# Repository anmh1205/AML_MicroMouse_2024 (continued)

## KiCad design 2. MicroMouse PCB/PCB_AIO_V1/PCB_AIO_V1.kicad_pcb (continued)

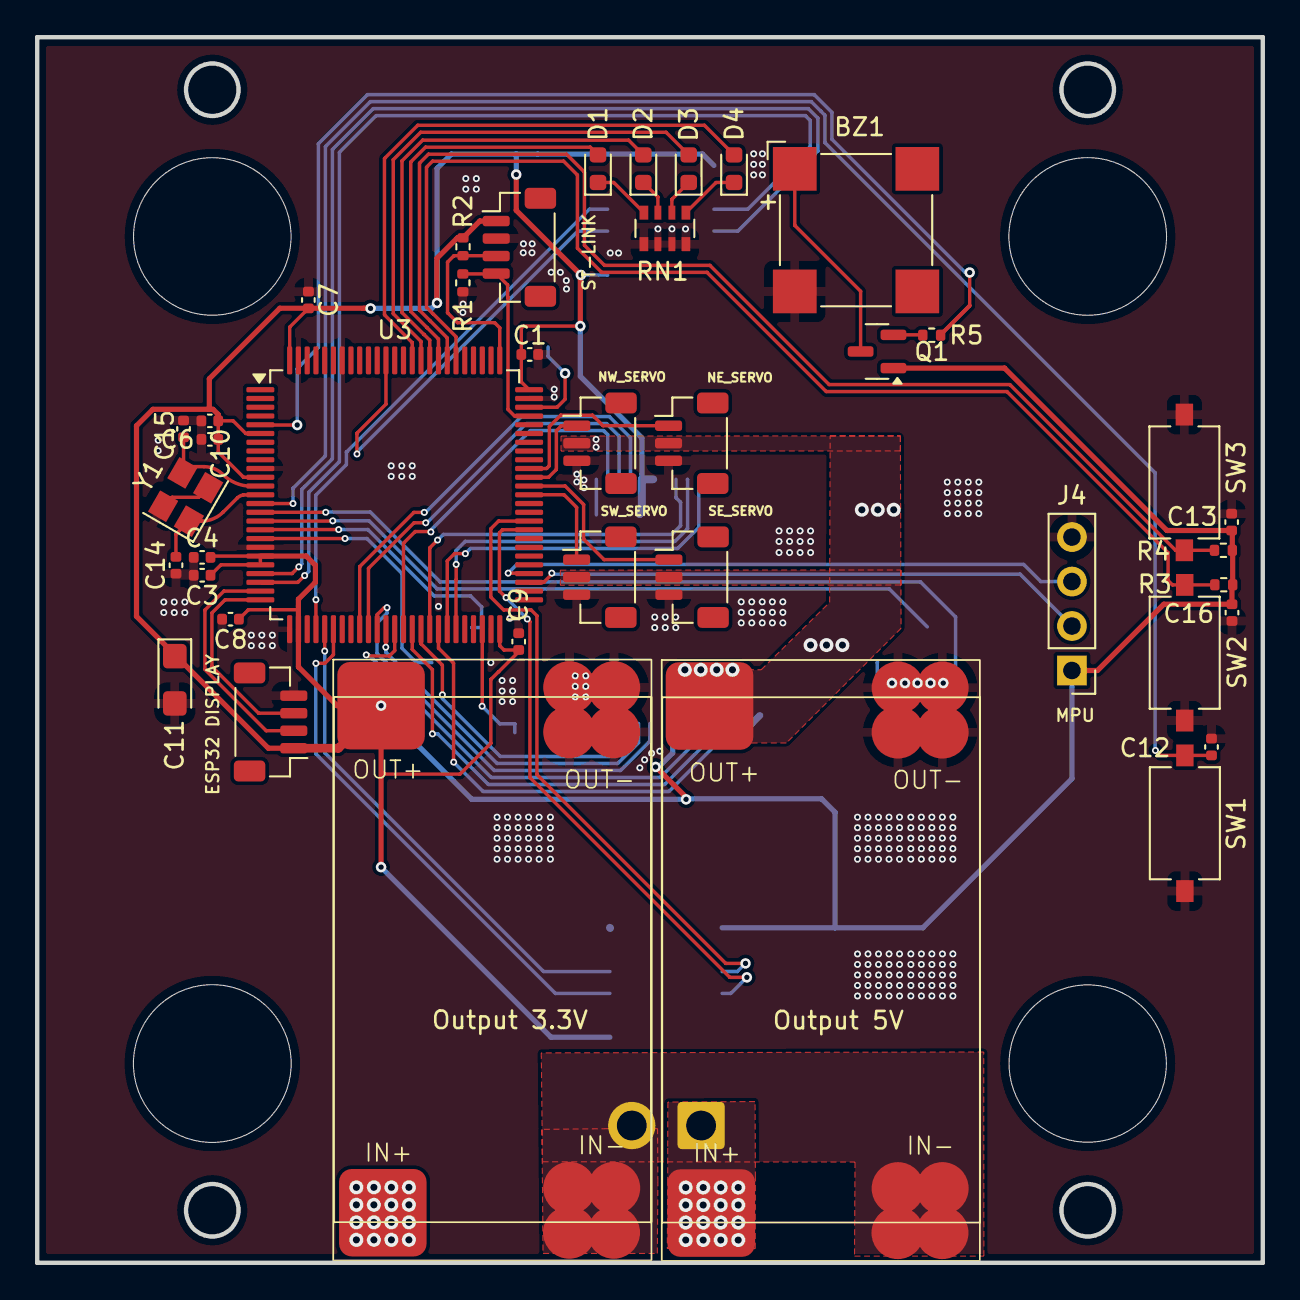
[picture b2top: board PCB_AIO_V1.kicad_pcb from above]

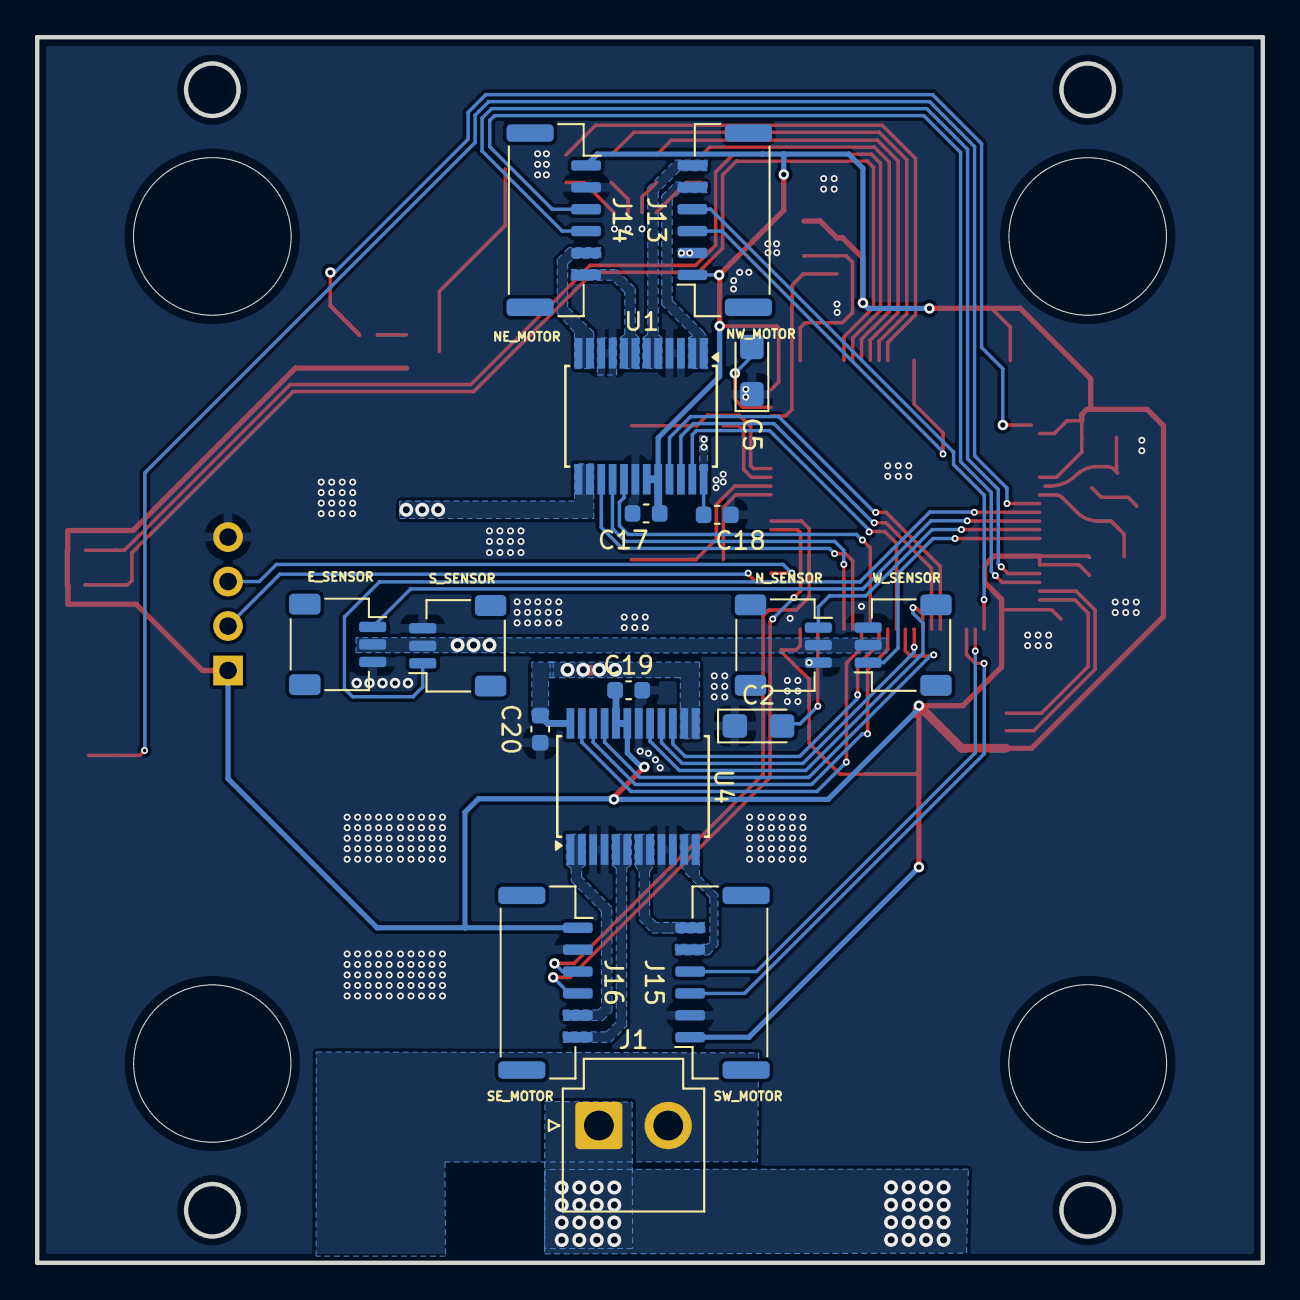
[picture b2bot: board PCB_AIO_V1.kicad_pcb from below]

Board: 2 copper layers, 70.0 x 70.0 mm, 57 parts (17 on the bottom side), 65 nets.

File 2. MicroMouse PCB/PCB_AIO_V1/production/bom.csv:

Designator,Footprint,Quantity,Value,LCSC Part #
BZ1,MagneticBuzzer_CUI_CMT-8504-100-SMT,1,Buzzer,
"C1, C10, C12, C13, C16, C3, C4, C6, C7, C8, C9",0402,11,100nF,
C11,CP_EIA-3216-10_Kemet-I,1,4.7uF,
"C14, C15",0402,2,15pF,
"C17, C18, C19, C20",0603,4,10uF,
"C2, C5",CP_EIA-3216-10_Kemet-I,2,2.2uF,
"D1, D2, D3, D4",0603,4,3VL,
J1,JST_VH_B2P-VH-B_1x02_P3.96mm_Vertical,1,Conn_01x02_Pin,
"J10, J11, J12, J9",JST_SH_SM03B-SRSS-TB_1x03-1MP_P1.00mm_Horizontal,4,Conn_01x03_Pin,
"J13, J14, J15, J16",JST_GH_SM06B-GHS-TB_1x06-1MP_P1.25mm_Horizontal,4,Conn_01x06_Pin,
J2,JST_SH_BM04B-SRSS-TB_1x04-1MP_P1.00mm_Vertical,1,STLINK,
J3,JST_SH_BM04B-SRSS-TB_1x04-1MP_P1.00mm_Vertical,1,MPU,
J4,PinHeader_1x04_P2.54mm_Vertical,1,MPU,
"J5, J6, J7, J8",JST_SH_BM03B-SRSS-TB_1x03-1MP_P1.00mm_Vertical,4,Conn_01x03_Pin,
Q1,SOT-23,1,S8550,
"R1, R2",0402,2,10K,
"R3, R4, R5",0402,3,1K,
RN1,R_Array_Convex_4x0603,1,R_Pack04,
"SW1, SW2, SW3",SW_Tactile_SPST_NO_Straight_CK_PTS636Sx25SMTRLFS,3,SW_Push,
"U1, U4",SSOP-24_5.3x8.2mm_P0.65mm,2,TB6612FNG,
U2,Mini560_5A,1,Output 5V,
U3,LQFP-100_14x14mm_P0.5mm,1,STM32H743VITx,
U5,Mini560_5A,1,Output 3.3V,
Y1,Crystal_SMD_3225-4Pin_3.2x2.5mm,1,Crystal_GND24_Small,

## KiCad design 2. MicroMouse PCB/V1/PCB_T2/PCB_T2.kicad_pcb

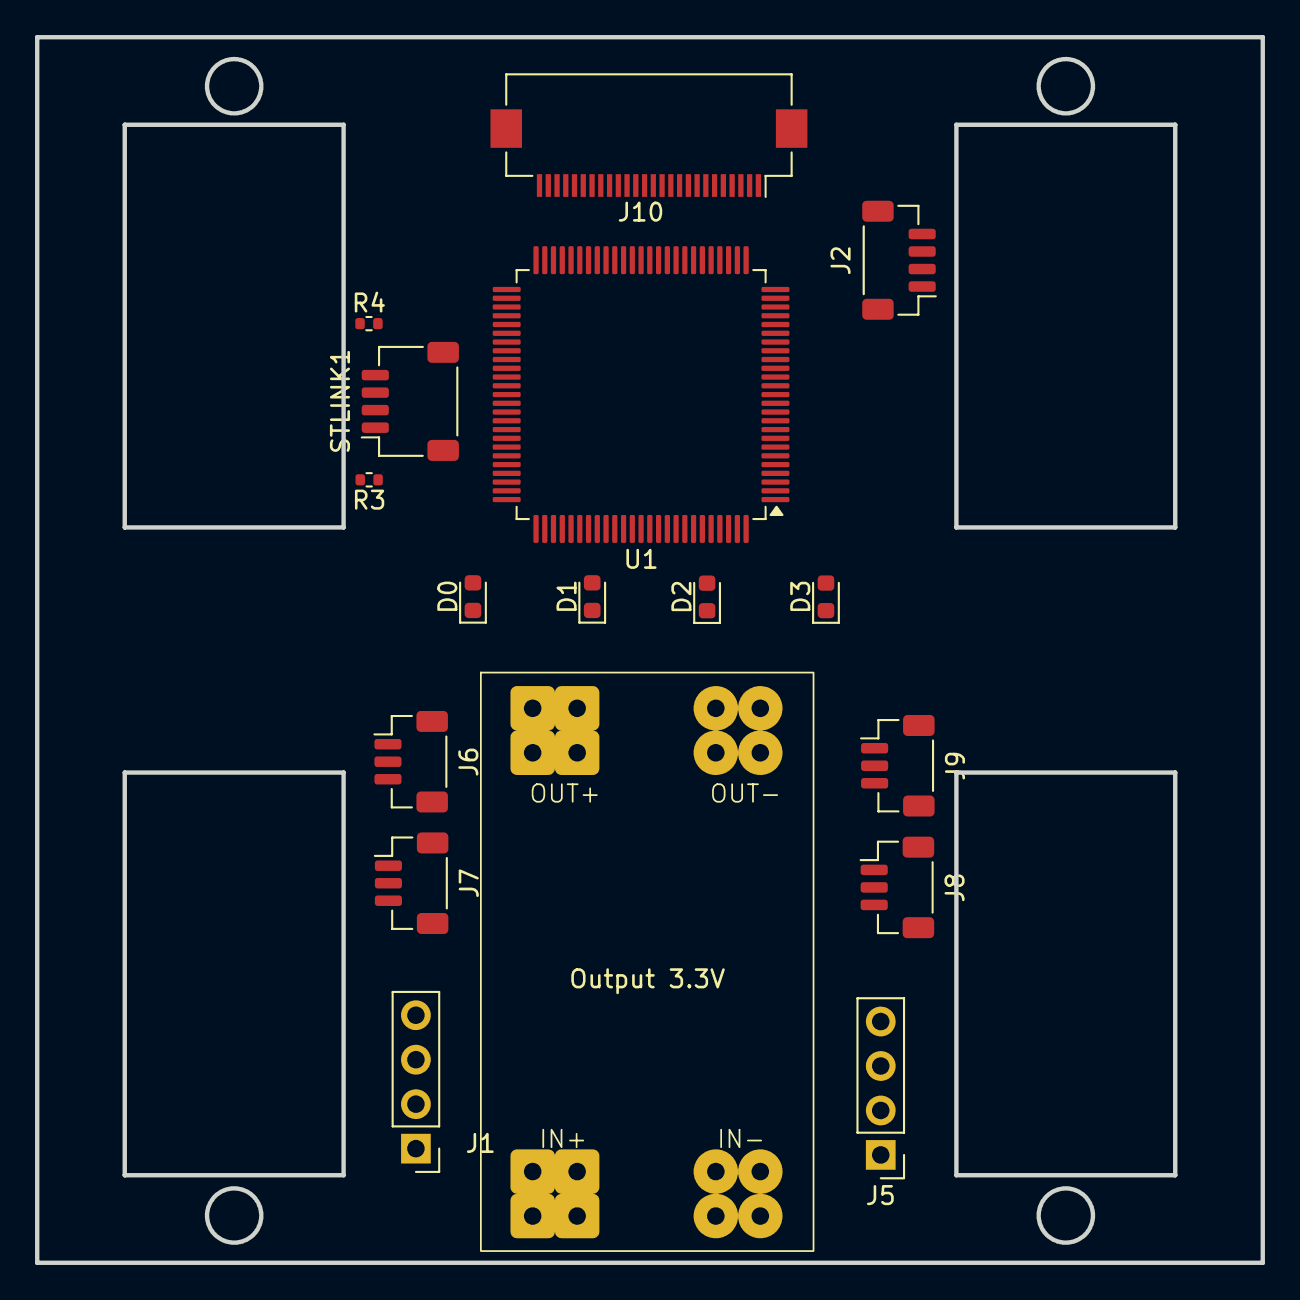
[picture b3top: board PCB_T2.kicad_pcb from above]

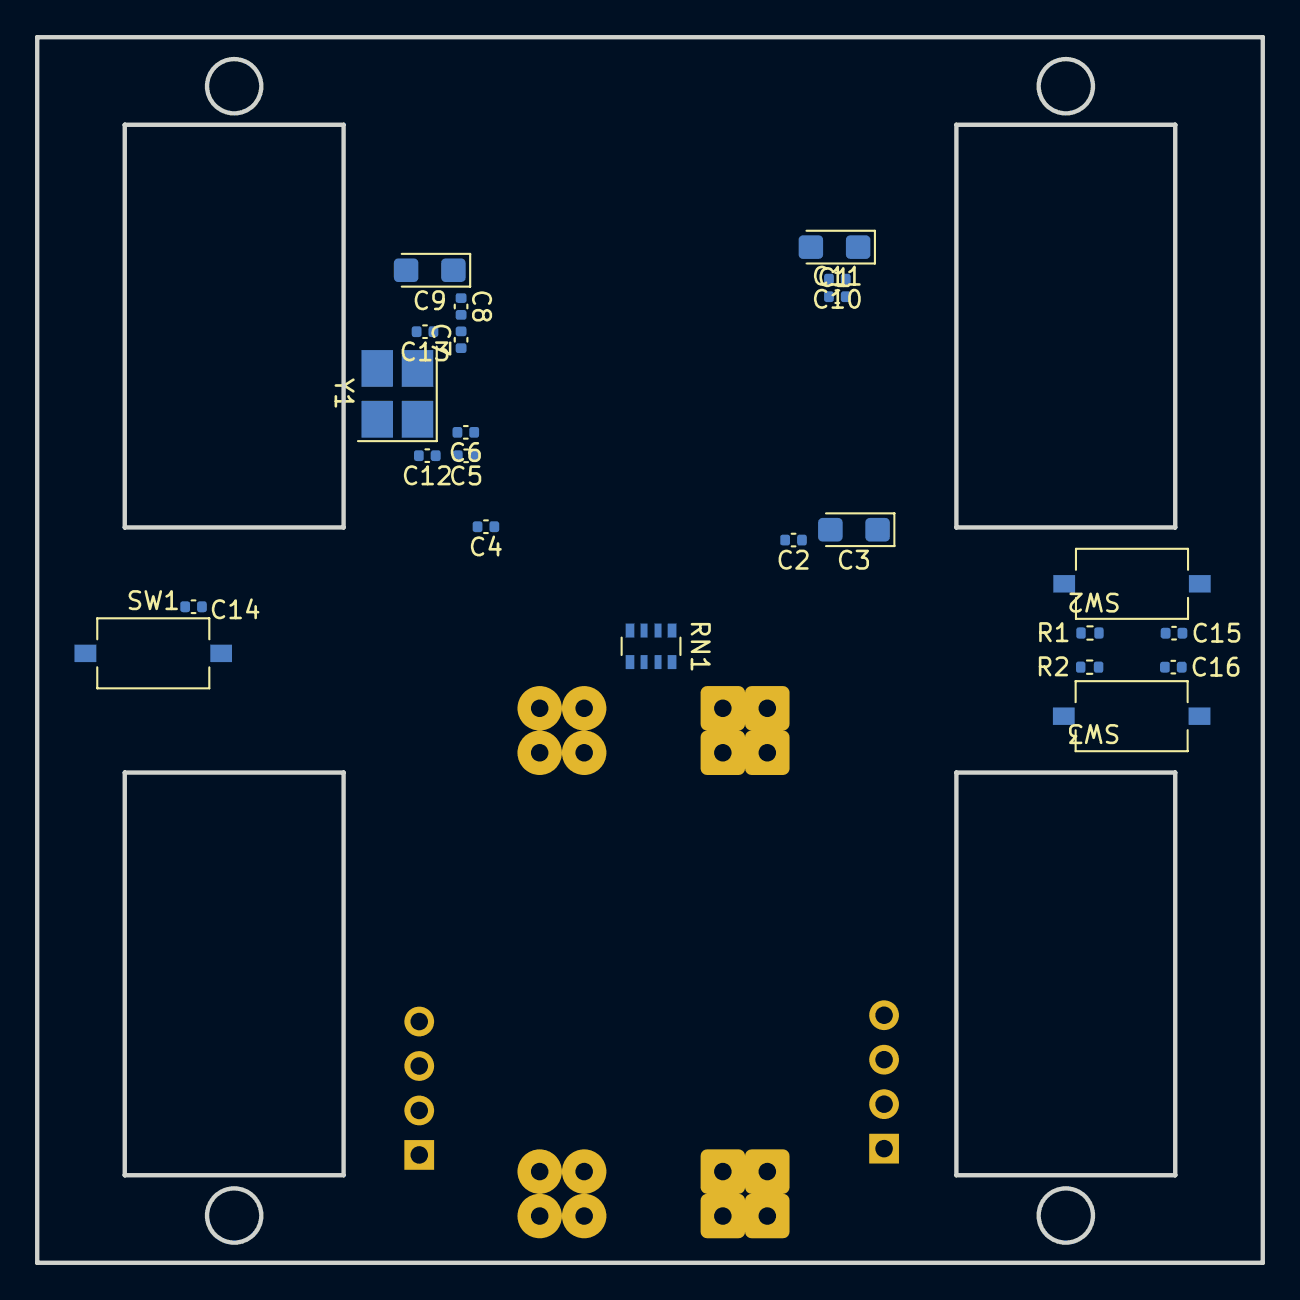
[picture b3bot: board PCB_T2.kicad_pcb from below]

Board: 2 copper layers, 70.0 x 70.0 mm, 40 parts (23 on the bottom side), 52 nets, no tracks yet.

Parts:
C1, C3: 2.2uF; CP_EIA-3216-10_Kemet-I
C2, C4, C5, C6, C7, C8, C10, C11, C14, C15, C16: 100nF; C_0402_1005Metric
C9: 4.7uF; CP_EIA-3216-10_Kemet-I
C12, C13: 15pF; C_0402_1005Metric
D0, D1, D2, D3: 3VL; LED_0603_1608Metric
J1: MPU; PinHeader_1x04_P2.54mm_Vertical
J2: MPU; JST_SH_BM04B-SRSS-TB_1x04-1MP_P1.00mm_Vertical
J5: Conn_01x04_Pin; PinHeader_1x04_P2.54mm_Vertical
J6, J7, J8, J9: Conn_01x03_Pin; JST_SH_BM03B-SRSS-TB_1x03-1MP_P1.00mm_Vertical
J10: Conn_01x26_Socket; Hirose_FH12-26S-0.5SH_1x26-1MP_P0.50mm_Horizontal
R1, R2: 1K; R_0402_1005Metric
R3, R4: 10K; R_0402_1005Metric
RN1: R_Pack04; R_Array_Convex_4x0603
STLINK1: STLINK; JST_SH_SM04B-SRSS-TB_1x04-1MP_P1.00mm_Horizontal
SW1, SW2, SW3: SW_Push; SW_Tactile_SPST_NO_Straight_CK_PTS636Sx25SMTRLFS
U1: STM32H743VIT6; LQFP-100_14x14mm_P0.5mm
U2: Output 3.3V; Mini560_5A
Y1: 48MHz; Crystal_SMD_3225-4Pin_3.2x2.5mm_HandSoldering

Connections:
+3.3V: C2.2, C4.1, C5.1, C6.1, C7.1, C8.1, C9.1, C10.2, C11.1, C15.2, C16.2, J1.1, J2.1, R1.2, R2.2, R3.2, STLINK1.1, U1.6 (VBAT), U1.11 (VDD), U1.19 (VDD), U1.21 (VREF+), U1.22 (VDDA), U1.28 (VDD), U1.50 (VDD), U1.75 (VDD), U1.100 (VDD)
+5V: J5.3, J6.2, J7.2, J8.2, J9.2
/BUTTON_0: R1.1, SW2.2, U1.81 (PD0)
/BUTTON_1: R2.1, SW3.2, U1.82 (PD1)
/E_TOF: J10.4, U1.18 (PC3)
/LED_0: D0.2 (A), U1.83 (PD2)
/LED_1: D1.2 (A), U1.84 (PD3)
/LED_2: D2.2 (A), U1.85 (PD4)
/LED_3: D3.2 (A), U1.86 (PD5)
/NE_ENC_A: J10.23, U1.23 (PA0)
/NE_ENC_B: J10.24, U1.24 (PA1)
/NE_IN1: J10.20, U1.43 (PE12)
/NE_IN2: J10.21, U1.46 (PE15)
/NE_PWM: J10.22, U1.45 (PE14)
/NE_SERVO: J9.1, U1.66 (PC9)
/NRST: C14.2, SW1.2, U1.14 (NRST)
/NW_ENC_A: J10.8, U1.30 (PA5)
/NW_ENC_B: J10.9, U1.89 (PB3)
/NW_IN1: J10.5, U1.35 (PB0)
/NW_IN2: J10.6, U1.36 (PB1)
/NW_PWM: J10.7, U1.40 (PE9)
/NW_SERVO: J6.1, U1.63 (PC6)
/N_TOF: J10.1, U1.15 (PC0)
/PH0: C12.2, U1.12 (PH0), Y1.1
/PH1: C13.2, U1.13 (PH1), Y1.2
/SE_ENC_A: J10.18, U1.59 (PD12)
/SE_ENC_B: J10.19, U1.60 (PD13)
/SE_IN1: J10.15, U1.39 (PE8)
/SE_IN2: J10.16, U1.41 (PE10)
/SE_PWM: J10.17, U1.44 (PE13)
/SE_SERVO: J8.1, U1.65 (PC8)
/SWCLK: R3.1, STLINK1.3, U1.76 (PA14)
/SWDIO: R4.2, STLINK1.4, U1.72 (PA13)
/SW_ENC_A: J10.13, U1.31 (PA6)
/SW_ENC_B: J10.14, U1.32 (PA7)
/SW_IN1: J10.10, U1.37 (PB2)
/SW_IN2: J10.11, U1.38 (PE7)
/SW_PWM: J10.12, U1.42 (PE11)
/SW_SERVO: J7.1, U1.64 (PC7)
/S_TOF: J10.3, U1.17 (PC2)
/USART1_RX: J1.3, U1.54 (PB15)
/USART1_TX: J1.2, U1.53 (PB14)
/USART2_RX: J2.3, U1.26 (PA3)
/USART2_TX: J2.2, U1.25 (PA2)
/W_TOF: J10.2, U1.16 (PC1)
GND: C1.1, C2.1, C3.1, C4.2, C5.2, C6.2, C7.2, C8.2, C9.2, C10.1, C11.2, C12.1, C13.1, C14.1, C15.1, C16.1, J1.4, J2.4, J5.4, J6.3, J7.3, J8.3, J9.3, R4.1, RN1.5 (R4.2), RN1.6 (R3.2), RN1.7 (R2.2), RN1.8 (R1.2), STLINK1.2, SW1.1, SW2.1, SW3.1, U1.10 (VSS), U1.20 (VSSA), U1.27 (VSS), U1.74 (VSS), U1.94 (BOOT0), U1.99 (VSS)
unnamed: D0.1 (K), RN1.1 (R1.1)
unnamed: D1.1 (K), RN1.2 (R2.1)
unnamed: D2.1 (K), RN1.3 (R3.1)
unnamed: D3.1 (K), RN1.4 (R4.1)
unnamed: C1.2, U1.49 (VCAP_1)
unnamed: C3.2, U1.73 (VCAP_2)

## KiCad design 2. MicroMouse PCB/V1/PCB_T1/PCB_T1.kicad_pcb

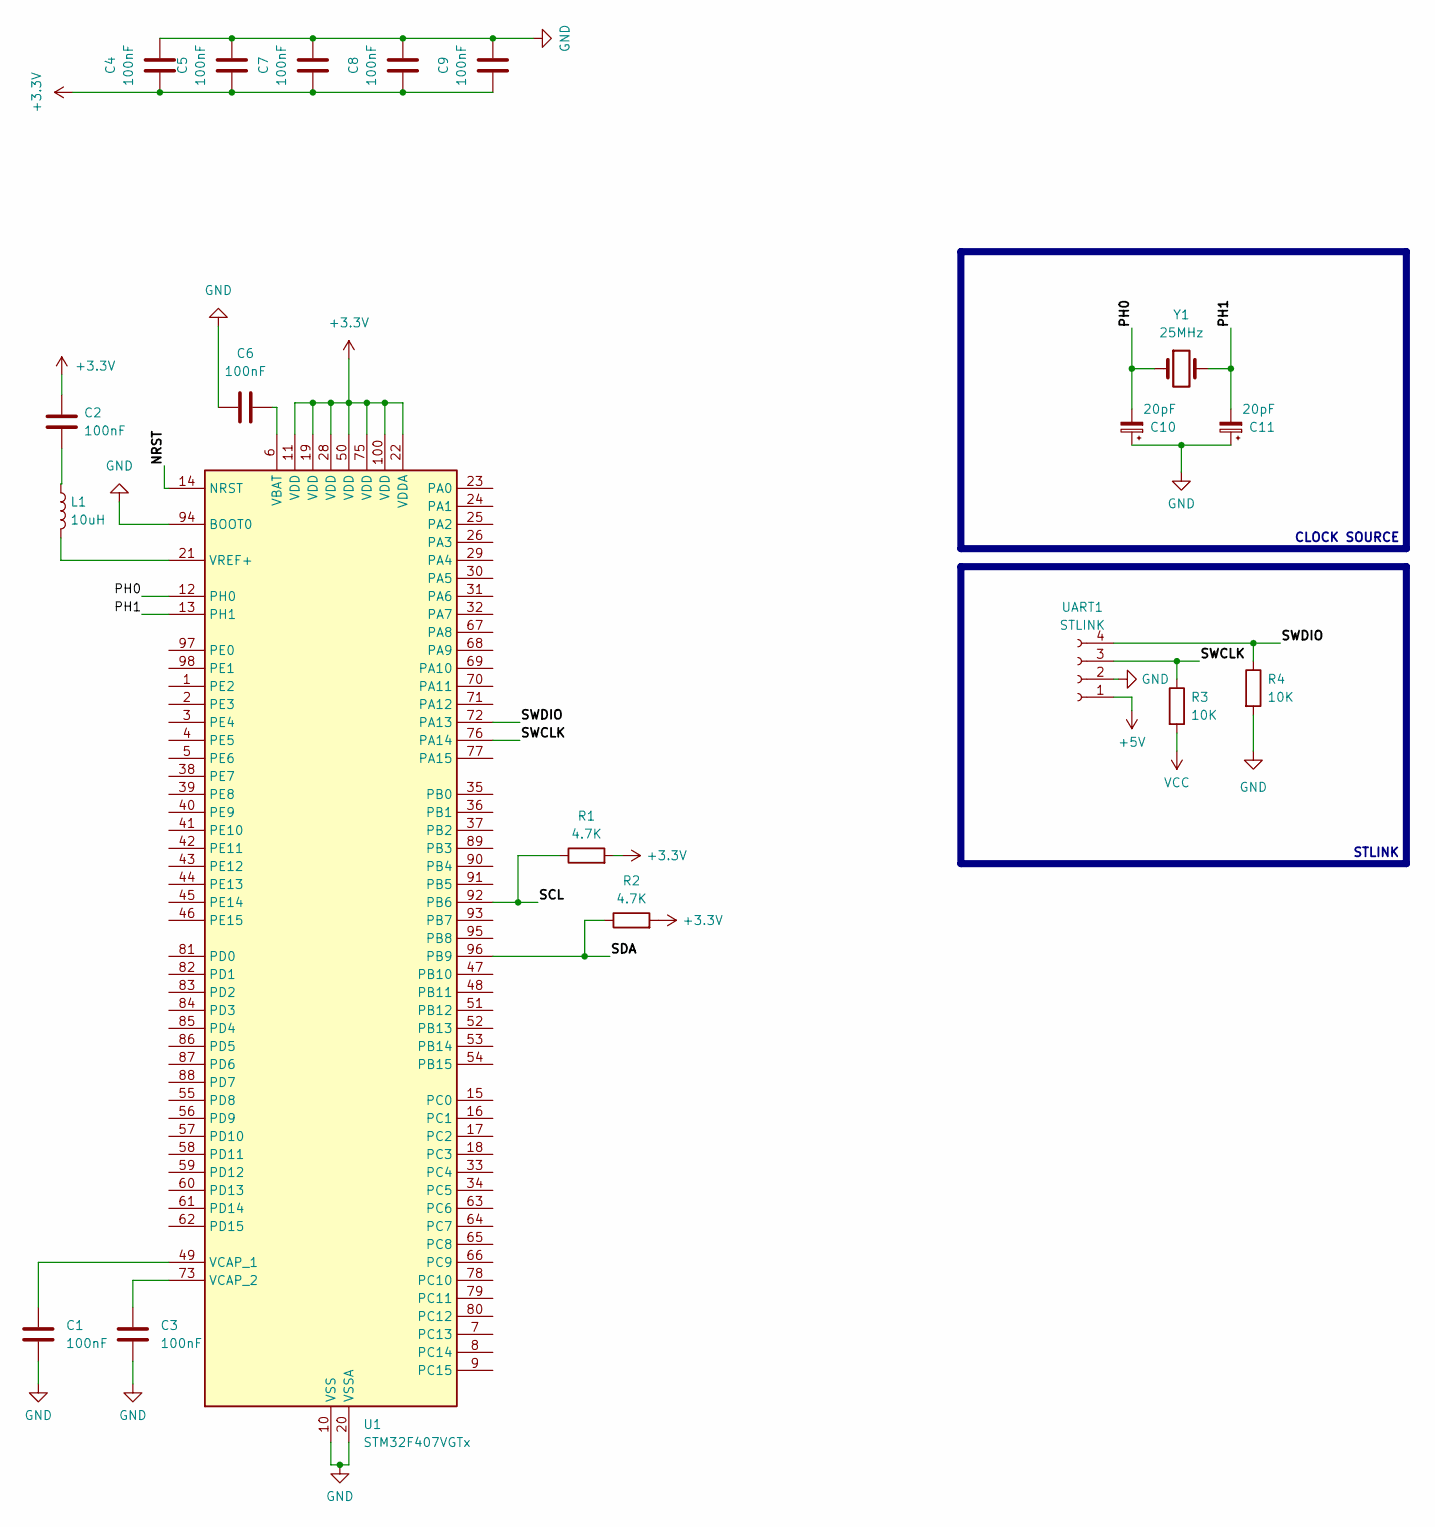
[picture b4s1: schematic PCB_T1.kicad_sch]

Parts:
C1, C2, C3, C4, C5, C6, C7, C8, C9: 100nF; C_0603_1608Metric
C10, C11: 20pF; C_0603_1608Metric
L1: 10uH; C_0805_2012Metric_Pad1.18x1.45mm_HandSolder
R1, R2: 4.7K; R_0603_1608Metric
R3, R4: 10K; R_0603_1608Metric
U1: STM32F407VGTx; LQFP-100_14x14mm_P0.5mm
UART1: STLINK; JST 4
Y1: 25MHz; Crystal_HC49-U_Vertical

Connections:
+3.3V: C2.1, C4.1, C5.1, C7.1, C8.1, C9.1, R1.2, R2.2, U1.11 (VDD), U1.19 (VDD), U1.22 (VDDA), U1.28 (VDD), U1.50 (VDD), U1.75 (VDD), U1.100 (VDD)
/NRST: U1.14 (NRST)
/PH0: C10.2, U1.12 (PH0), Y1.1
/PH1: C11.2, U1.13 (PH1), Y1.2
/SCL: R1.1, U1.92 (PB6)
/SDA: R2.1, U1.96 (PB9)
/SWCLK: R3.1, U1.76 (PA14), UART1.3
/SWDIO: R4.1, U1.72 (PA13), UART1.4
GND: C1.1, C3.1, C4.2, C5.2, C6.1, C7.2, C8.2, C9.2, C10.1, C11.1, R4.2, U1.10 (VSS), U1.20 (VSSA), U1.27 (VSS), U1.74 (VSS), U1.94 (BOOT0), U1.99 (VSS), UART1.2
unnamed: C2.2, L1.1
unnamed: C6.2, U1.6 (VBAT)
unnamed: C1.2, U1.49 (VCAP_1)
unnamed: C3.2, U1.73 (VCAP_2)
unnamed: L1.2, U1.21 (VREF+)
VCC: R3.2

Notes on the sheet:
STLINK
CLOCK SOURCE

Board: 2 copper layers, 18 parts (0 on the bottom side), 13 nets, no tracks yet.

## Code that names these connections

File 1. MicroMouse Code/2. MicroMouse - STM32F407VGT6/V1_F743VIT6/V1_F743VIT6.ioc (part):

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Mcu.Name=STM32H743VITx
Mcu.Package=LQFP100
Mcu.UserName=STM32H743VITx
PA0.GPIOParameters=GPIO_Label
PA0.GPIO_Label=NE_ENC_A
PA0.Signal=S_TIM5_CH1
PA1.GPIOParameters=GPIO_Label
PA1.GPIO_Label=NE_ENC_B
PA1.Signal=S_TIM5_CH2
PA13\ (JTMS/SWDIO).Mode=Serial_Wire
PA13\ (JTMS/SWDIO).Signal=DEBUG_JTMS-SWDIO
PA14\ (JTCK/SWCLK).Mode=Serial_Wire
PA14\ (JTCK/SWCLK).Signal=DEBUG_JTCK-SWCLK
PA2.Mode=Asynchronous
PA2.Signal=USART2_TX
PA3.Mode=Asynchronous
PA3.Signal=USART2_RX
PA5.GPIOParameters=GPIO_Label
PA5.GPIO_Label=NW_ENC_A
PA5.Signal=S_TIM2_CH1_ETR
PA6.GPIOParameters=GPIO_Label
PA6.GPIO_Label=SW_ENC_A
PA6.Signal=S_TIM3_CH1
PA7.GPIOParameters=GPIO_Label
PA7.GPIO_Label=SW_ENC_B
PA7.Signal=S_TIM3_CH2
PB0.GPIOParameters=GPIO_Label
PB0.GPIO_Label=NW_IN1
PB0.Signal=GPIO_Output
PB1.GPIOParameters=GPIO_Label
PB1.GPIO_Label=NW_IN2
PB1.Signal=GPIO_Output
PB14.Mode=Asynchronous
PB14.Signal=USART1_TX
PB15.Mode=Asynchronous
PB15.Signal=USART1_RX
PB2.GPIOParameters=GPIO_Label
PB2.GPIO_Label=SW_IN1
PB2.Signal=GPIO_Output
PB3\ (JTDO/TRACESWO).GPIOParameters=GPIO_Label
PB3\ (JTDO/TRACESWO).GPIO_Label=NW_ENC_B
PB3\ (JTDO/TRACESWO).Signal=S_TIM2_CH2
PB6.Mode=I2C
PB6.Signal=I2C1_SCL
PB7.Mode=I2C
PB7.Signal=I2C1_SDA
PB8.Mode=I2C
PB8.Signal=I2C4_SCL
PB9.Mode=I2C
PB9.Signal=I2C4_SDA
PC0.GPIOParameters=GPIO_Label
PC0.GPIO_Label=N_TOF
PC0.Signal=ADCx_INP10
PC1.GPIOParameters=GPIO_Label
PC1.GPIO_Label=W_TOF
PC1.Signal=ADCx_INP11
PC2_C.GPIOParameters=GPIO_Label
PC2_C.GPIO_Label=S_TOF
PC2_C.Mode=IN0-Single-Ended
PC2_C.Signal=ADC3_INP0
PC3_C.GPIOParameters=GPIO_Label
PC3_C.GPIO_Label=E_TOF
PC3_C.Mode=IN1-Single-Ended
PC3_C.Signal=ADC3_INP1
PC6.GPIOParameters=GPIO_Label
PC6.GPIO_Label=NW_SERVO
PC6.Signal=S_TIM8_CH1
PC7.GPIOParameters=GPIO_Label
PC7.GPIO_Label=SW_SERVO
PC7.Signal=S_TIM8_CH2
PC8.GPIOParameters=GPIO_Label
PC8.GPIO_Label=SE_SERVO
PC8.Signal=S_TIM8_CH3
PC9.GPIOParameters=GPIO_Label
PC9.GPIO_Label=NE_SERVO
PC9.Signal=S_TIM8_CH4
PD0.GPIOParameters=GPIO_Label
PD0.GPIO_Label=BUTTON_0
PD0.Signal=GPXTI0
PD1.GPIOParameters=GPIO_Label
PD1.GPIO_Label=BUTTON_1
PD1.Signal=GPXTI1
PD12.GPIOParameters=GPIO_Label
PD12.GPIO_Label=SE_ENC_A
PD12.Signal=S_TIM4_CH1
PD13.GPIOParameters=GPIO_Label
PD13.GPIO_Label=SE_ENC_B
PD13.Signal=S_TIM4_CH2
PD2.GPIOParameters=GPIO_Label
PD2.GPIO_Label=LED_0
PD2.Signal=GPIO_Output
PD3.GPIOParameters=GPIO_Label
PD3.GPIO_Label=LED_1
PD3.Signal=GPIO_Output
PD4.GPIOParameters=GPIO_Label
PD4.GPIO_Label=LED_2
PD4.Signal=GPIO_Output
PD5.GPIOParameters=GPIO_Label
PD5.GPIO_Label=LED_3
PD5.Signal=GPIO_Output
PD8.Mode=Asynchronous
PD8.Signal=USART3_TX
PD9.Mode=Asynchronous
PD9.Signal=USART3_RX
PE10.GPIOParameters=GPIO_Label
PE10.GPIO_Label=SE_IN2
PE10.Signal=GPIO_Output
PE11.GPIOParameters=GPIO_Label
PE11.GPIO_Label=SW_PWM
PE11.Signal=S_TIM1_CH2
PE12.GPIOParameters=GPIO_Label
PE12.GPIO_Label=NE_IN1
PE12.Signal=GPIO_Output
PE13.GPIOParameters=GPIO_Label
PE13.GPIO_Label=SE_PWM
PE13.Signal=S_TIM1_CH3
PE14.GPIOParameters=GPIO_Label
PE14.GPIO_Label=NE_PWM
PE14.Signal=S_TIM1_CH4
PE15.GPIOParameters=GPIO_Label
PE15.GPIO_Label=NE_IN2
PE15.Signal=GPIO_Output
PE5.Signal=S_TIM15_CH1
PE7.GPIOParameters=GPIO_Label
PE7.GPIO_Label=SW_IN2
PE7.Signal=GPIO_Output
PE8.GPIOParameters=GPIO_Label
PE8.GPIO_Label=SE_IN1
PE8.Signal=GPIO_Output
PE9.GPIOParameters=GPIO_Label
PE9.GPIO_Label=NW_PWM
PE9.Signal=S_TIM1_CH1
PH0-OSC_IN\ (PH0).Mode=HSE-External-Oscillator
PH0-OSC_IN\ (PH0).Signal=RCC_OSC_IN
PH1-OSC_OUT\ (PH1).Mode=HSE-External-Oscillator
PH1-OSC_OUT\ (PH1).Signal=RCC_OSC_OUT
RCC.HSE_VALUE=48000000
RCC.SYSCLKFreq_VALUE=480000000
RCC.SYSCLKSource=RCC_SYSCLKSOURCE_PLLCLK
board=custom

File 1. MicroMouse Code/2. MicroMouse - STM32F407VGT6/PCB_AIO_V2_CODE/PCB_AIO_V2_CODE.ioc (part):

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Mcu.Name=STM32H743VITx
Mcu.Package=LQFP100
Mcu.UserName=STM32H743VITx
PA0.GPIOParameters=GPIO_Label
PA0.GPIO_Label=RIGHT_ENCODER_A
PA0.Signal=S_TIM5_CH1
PA1.GPIOParameters=GPIO_Label
PA1.GPIO_Label=RIGHT_ENCODER_B
PA1.Signal=S_TIM5_CH2
PA13\ (JTMS/SWDIO).Mode=Serial_Wire
PA13\ (JTMS/SWDIO).Signal=DEBUG_JTMS-SWDIO
PA14\ (JTCK/SWCLK).Mode=Serial_Wire
PA14\ (JTCK/SWCLK).Signal=DEBUG_JTCK-SWCLK
PA15\ (JTDI).GPIOParameters=GPIO_Label
PA15\ (JTDI).GPIO_Label=LEFT_ENCODER_A
PA15\ (JTDI).Signal=S_TIM2_CH1_ETR
PA2.GPIOParameters=GPIO_Label
PA2.GPIO_Label=IR_SENSOR_BR
PA2.Signal=ADCx_INP14
PA3.GPIOParameters=GPIO_Label
PA3.GPIO_Label=IR_SENSOR_BL
PA3.Signal=ADCx_INP15
PA6.GPIOParameters=GPIO_Label
PA6.GPIO_Label=IR_SENSOR_RL
PA6.Signal=ADCx_INP3
PB1.GPIOParameters=GPIO_Label
PB1.GPIO_Label=IR_SENSOR_FF
PB1.Signal=ADCx_INP5
PB14.Mode=Asynchronous
PB14.Signal=USART1_TX
PB15.Mode=Asynchronous
PB15.Signal=USART1_RX
PB3\ (JTDO/TRACESWO).GPIOParameters=GPIO_Label
PB3\ (JTDO/TRACESWO).GPIO_Label=LEFT_ENCODER_B
PB3\ (JTDO/TRACESWO).Signal=S_TIM2_CH2
PC0.GPIOParameters=GPIO_Label
PC0.GPIO_Label=IR_SENSOR_FR
PC0.Signal=ADCx_INP10
PC1.GPIOParameters=GPIO_Label
PC1.GPIO_Label=IR_SENSOR_RR
PC1.Signal=ADCx_INP11
PC4.GPIOParameters=GPIO_Label
PC4.GPIO_Label=IR_SENSOR_FL
PC4.Signal=ADCx_INP4
PC6.Signal=S_TIM3_CH1
PD0.GPIOParameters=GPIO_Label
PD0.GPIO_Label=LED_0
PD0.Signal=GPIO_Output
PD1.GPIOParameters=GPIO_Label
PD1.GPIO_Label=LED_1
PD1.Signal=GPIO_Output
PD2.GPIOParameters=GPIO_Label
PD2.GPIO_Label=LED_2
PD2.Signal=GPIO_Output
PD3.GPIOParameters=GPIO_Label
PD3.GPIO_Label=LED_3
PD3.Signal=GPIO_Output
PE0.GPIOParameters=GPIO_Label
PE0.GPIO_Label=BUTTON_0
PE0.Signal=GPXTI0
PE1.GPIOParameters=GPIO_Label
PE1.GPIO_Label=BUTTON_1
PE1.Signal=GPXTI1
PE11.GPIOParameters=GPIO_Label
PE11.GPIO_Label=RIGHT_MOTOR_PWM
PE11.Signal=S_TIM1_CH2
PE12.GPIOParameters=GPIO_Label
PE12.GPIO_Label=RIGHT_MOTOR_IN1
PE12.Signal=GPIO_Output
PE13.GPIOParameters=GPIO_Label
PE13.GPIO_Label=RIGHT_MOTOR_IN2
PE13.Signal=GPIO_Output
PE2.GPIOParameters=GPIO_PuPd,GPIO_Label
PE2.GPIO_Label=BIT_SW_0
PE2.GPIO_PuPd=GPIO_PULLDOWN
PE2.Signal=GPIO_Input
PE3.GPIOParameters=GPIO_PuPd,GPIO_Label
PE3.GPIO_Label=BIT_SW_1
PE3.GPIO_PuPd=GPIO_PULLDOWN
PE3.Signal=GPIO_Input
PE4.GPIOParameters=GPIO_PuPd,GPIO_Label
PE4.GPIO_Label=BIT_SW_2
PE4.GPIO_PuPd=GPIO_PULLDOWN
PE4.Signal=GPIO_Input
PE5.GPIOParameters=GPIO_PuPd,GPIO_Label
PE5.GPIO_Label=BIT_SW_3
PE5.GPIO_PuPd=GPIO_PULLDOWN
PE5.Signal=GPIO_Input
PE6.GPIOParameters=GPIO_PuPd,GPIO_Label
PE6.GPIO_Label=BIT_SW_4
PE6.GPIO_PuPd=GPIO_PULLDOWN
PE6.Signal=GPIO_Input
PE7.GPIOParameters=GPIO_Label
PE7.GPIO_Label=LEFT_MOTOR_IN1
PE7.Signal=GPIO_Output
PE8.GPIOParameters=GPIO_Label
PE8.GPIO_Label=LEFT_MOTOR_IN2
PE8.Signal=GPIO_Output
PE9.GPIOParameters=GPIO_Label
PE9.GPIO_Label=LEFT_MOTOR_PWM
PE9.Signal=S_TIM1_CH1
PH0-OSC_IN\ (PH0).Mode=HSE-External-Oscillator
PH0-OSC_IN\ (PH0).Signal=RCC_OSC_IN
PH1-OSC_OUT\ (PH1).Mode=HSE-External-Oscillator
PH1-OSC_OUT\ (PH1).Signal=RCC_OSC_OUT
RCC.HSE_VALUE=48000000
RCC.SYSCLKFreq_VALUE=480000000
RCC.SYSCLKSource=RCC_SYSCLKSOURCE_PLLCLK
board=custom

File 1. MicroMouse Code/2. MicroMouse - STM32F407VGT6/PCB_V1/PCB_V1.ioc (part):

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Mcu.Name=STM32F407V(E-G)Tx
Mcu.Package=LQFP100
Mcu.UserName=STM32F407VETx
PA1.Signal=S_TIM2_CH2
PA13.Mode=Serial_Wire
PA13.Signal=SYS_JTMS-SWDIO
PA14.Mode=Serial_Wire
PA14.Signal=SYS_JTCK-SWCLK
PA5.Signal=S_TIM2_CH1_ETR
PB10.GPIOParameters=GPIO_PuPd
PB10.GPIO_PuPd=GPIO_PULLUP
PB10.Mode=Asynchronous
PB10.Signal=USART3_TX
PB11.GPIOParameters=GPIO_PuPd
PB11.GPIO_PuPd=GPIO_PULLUP
PB11.Mode=Asynchronous
PB11.Signal=USART3_RX
PB3.GPIOParameters=GPIO_Label
PB3.GPIO_Label=XSHUT_FL
PB3.Signal=GPIO_Output
PB6.GPIOParameters=GPIO_Pu
PB6.GPIO_Pu=GPIO_NOPULL
PB6.Mode=I2C
PB6.Signal=I2C1_SCL
PB7.Signal=S_TIM4_CH2
PB9.GPIOParameters=GPIO_Pu
PB9.GPIO_Pu=GPIO_NOPULL
PB9.Mode=I2C
PB9.Signal=I2C1_SDA
PC0.Signal=GPIO_Output
PC1.Signal=GPIO_Output
PC10.Signal=GPIO_Output
PC12.GPIOParameters=GPIO_Label
PC12.GPIO_Label=STBY
PC12.Signal=GPIO_Output
PC2.Signal=GPIO_Output
PC3.Signal=GPIO_Output
PC4.Signal=GPIO_Output
PC5.Signal=GPIO_Output
PC6.Mode=Asynchronous
PC6.Signal=USART6_TX
PC7.Mode=Asynchronous
PC7.Signal=USART6_RX
PC8.Signal=GPIO_Output
PD0.GPIOParameters=GPIO_Label
PD0.GPIO_Label=XSHUT_FF
PD0.Signal=GPIO_Output
PD1.GPIOParameters=GPIO_Label
PD1.GPIO_Label=BIN2
PD1.Signal=GPIO_Output
PD12.Signal=S_TIM4_CH1
PD13.Signal=GPIO_Output
PD2.GPIOParameters=GPIO_Label
PD2.GPIO_Label=XSHUT_BR
PD2.Signal=GPIO_Output
PD3.GPIOParameters=GPIO_Label
PD3.GPIO_Label=BIN1
PD3.Signal=GPIO_Output
PD4.GPIOParameters=GPIO_Label
PD4.GPIO_Label=XSHUT_BL
PD4.Signal=GPIO_Output
PD5.GPIOParameters=GPIO_Label
PD5.GPIO_Label=AIN2
PD5.Signal=GPIO_Output
PD6.GPIOParameters=GPIO_Label
PD6.GPIO_Label=XSHUT_FR
PD6.Signal=GPIO_Output
PD7.GPIOParameters=GPIO_Label
PD7.GPIO_Label=AIN1
PD7.Signal=GPIO_Output
PD8.GPIOParameters=PinState,GPIO_PuPd,GPIO_Label,GPIO_ModeDefaultOutputPP
PD8.GPIO_Label=BUZZER
PD8.GPIO_ModeDefaultOutputPP=GPIO_MODE_OUTPUT_OD
PD8.GPIO_PuPd=GPIO_NOPULL
PD8.PinState=GPIO_PIN_SET
PD8.Signal=GPIO_Output
PE1.Signal=GPXTI1
PE11.Signal=S_TIM1_CH2
PE2.Signal=GPXTI2
PE3.Signal=GPXTI3
PE4.Signal=GPXTI4
PE5.Signal=GPXTI5
PE9.Signal=S_TIM1_CH1
PH0-OSC_IN.Mode=HSE-External-Oscillator
PH0-OSC_IN.Signal=RCC_OSC_IN
PH1-OSC_OUT.Mode=HSE-External-Oscillator
PH1-OSC_OUT.Signal=RCC_OSC_OUT
RCC.HSE_VALUE=25000000
RCC.SYSCLKFreq_VALUE=168000000
RCC.SYSCLKSource=RCC_SYSCLKSOURCE_PLLCLK
board=custom

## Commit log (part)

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2024-08-10 add line 131 at main.c
2024-08-12 update PCB 12/08/2024
2024-08-13 update route tracks before change
2024-08-13 completed schematic of all in one PCB
2024-08-16 completed PCB_AIO_V1
2024-08-29 finish PCB_AIO_V1
2024-09-05 update before create dev branch
2024-09-05 moved stm32h743vit6
2024-09-08 completed schematic of PCB_AIO_V2
2024-09-12 completed PCB_AIO_V2
2024-09-12 updated logo AML
2024-09-13 SH 1.0 4P -> XH 2.54 4P
2024-10-23 completed PCB_AIO_V2 pin config
2024-10-30 - tested Buzzer - tested Led - tested MPU
2024-10-30 Date: 1AM 31/10/2023: - writing AML_MotorControl lib - completed AML_PID lib
2024-10-31 - tested encoder, TB6612FNG, bit switch, button, MPU, buzzer, led, ST-link - completed AML_PID lib - completed base of AML_MotorControl lib
2024-11-05 - tested all function of hardware
2024-11-05 test new branch
2024-11-05 test new branch #2
2024-11-05 - fix bug in AML_PID (not init limMin, limMax) - read 2_15 IR sensor function
2024-11-22 - integrated solve and queue library - completed config of debugger
2024-11-27 updated AML_MPUSensor --> AML_IMU
2024-11-29 - fixed some bug in AML_PID - removed AML_PID_Init - changed AML_PID_Struct variable
2024-12-05 completed flood fill algorithm (in MMS folder) - calculate first shortest path - calculate path for variable velocity
2024-12-07 - completed all function in MMS folder
2024-12-14 - added setPriorityHeading (MMS) - removed warning (PCB_AIO_V2)
2024-12-15 - changed heading macro (MMS) - changed MouseSpeed (new motor)
2024-12-15 test new branch (change pwm 80% - main.c)
2024-12-16 solver missing Cmake config
2024-12-22 - imported new version of solver library - added turn left fuction, turn right function, move forward function
2025-01-10 update 10/10/2025
2025-01-17 -fixed push queue (PCB_V1 and MMS) - changed linkedlist queue to array queue (malloc issues)
2025-01-29 fixed DMA issues (cant receive data)
2025-02-08 fix all bug in GoStraight5 function (PCB V1)
2025-02-09 PCB_V1: - fixed some bug - removed waring
2025-02-18 update PCB_V1
